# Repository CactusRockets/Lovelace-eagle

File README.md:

# Placas da aviônica para o foguete Lovelace-1KM

Nesse repositório temos os arquivos das placas que farão parte da aviônica do foguete Lovelace de 1km da Cactus Rockets Design.

### Descrição

Temos duas placas principais para esta aviônica:
- Placa de Processamento
- Placa de Acionamento

A placa de processamento é responsável pelo processamento dos dados dos módulos, armazenamento desses dados e telemetria. A placa de acionamento possui o circuito necessário para a correta ativação do Skib.

OBS.: Os arquivos das placas podems ser abertos por meio software Eagle da Autodesk.

### Esquemáticos e layouts

### Conexões entre placas

### Funcionamento

A placa de processamento contém um switch de ativação do sistema. No momento que o switch é pressionado, o sistema liga e faz a leitura dos módulos. Após cada leitura, ele armazena esses valores no microSD e envia esses dados via telemetria.

No momento que a placa de processamento detectar uma queda, ela envia um sinal para a placa de acionamento para que a mesma ative o Skib da parte de recuperação.

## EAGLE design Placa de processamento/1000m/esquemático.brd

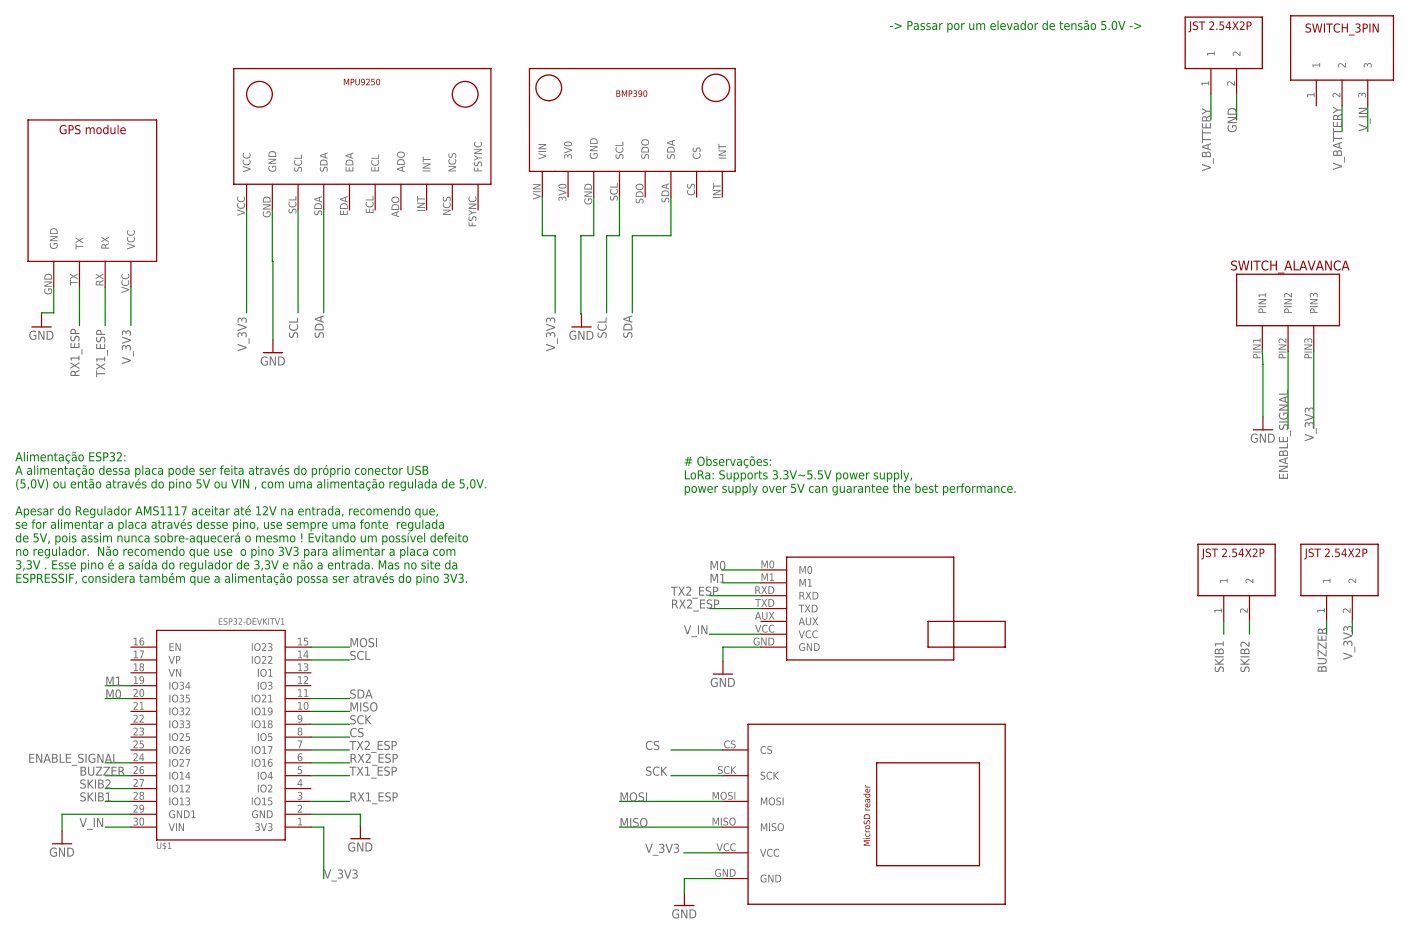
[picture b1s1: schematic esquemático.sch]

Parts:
U$1: ESP32DEVKITV1; ESP32-DEVKITV1
U$2: E22-400T30D; E22-400T30D_FOOTPRINT
U$3: GPS_MODULE; GPS_MODULE_FOOTPRINT
U$5: SWITCH_ALAVANCA; SWITCH_ALAVANCA_FOOTPRINT
U$7: MICROSD_READER; MICROSD_READER_FOOTPRINT
U$8, U$9, U$12: JST2.54X2P; JST2.54X2P_FOOTPRINT
U$10: MPU9250V1; MPU9250_FOOTPRINT
U$11: SWITCH_3PIN
U$13: BMP390V1; BMP390_FOOTPRINT

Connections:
BUZZER: U$1.26 (IO14), U$9.1
CS: U$1.8 (IO5), U$7.CS
ENABLE_SIGNAL: U$1.24 (IO27), U$5.PIN2
GND: U$1.2 (GND), U$1.29 (GND1), U$2.GND, U$3.GND, U$5.PIN1, U$7.GND, U$10.GND, U$12.2, U$13.GND
M0: U$1.20 (IO35), U$2.M0
M1: U$1.19 (IO34), U$2.M1
MISO: U$1.10 (IO19), U$7.MISO
MOSI: U$1.15 (IO23), U$7.MOSI
RX1_ESP: U$1.3 (IO15), U$3.TX
RX2_ESP: U$1.6 (IO16), U$2.TXD
SCK: U$1.9 (IO18), U$7.SCK
SCL: U$1.14 (IO22), U$10.SCL, U$13.SCL
SDA: U$1.11 (IO21), U$10.SDA, U$13.SDA
SKIB1: U$1.28 (IO13), U$8.1
SKIB2: U$1.27 (IO12), U$8.2
TX1_ESP: U$1.5 (IO4), U$3.RX
TX2_ESP: U$1.7 (IO17), U$2.RXD
V_3V3: U$1.1 (3V3), U$3.VCC, U$5.PIN3, U$7.VCC, U$9.2, U$10.VCC, U$13.VIN
V_BATTERY: U$11.2, U$12.1
V_IN: U$1.30 (VIN), U$2.VCC, U$11.3

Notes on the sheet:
-> Passar por um elevador de tensão 5.0V ->
# Observações: LoRa: Supports 3.3V~5.5V power supply, power supply over 5V can guarantee the best performance.
Alimentação ESP32: A alimentação dessa placa pode ser feita através do próprio conector USB (5,0V) ou então através do pino 5V ou VIN , com uma alimentação regulada de 5,0V. Apesar do Regulador AMS1117 aceitar até 12V na entrada, recomendo que, se for alimentar a placa através desse pino, use sempr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

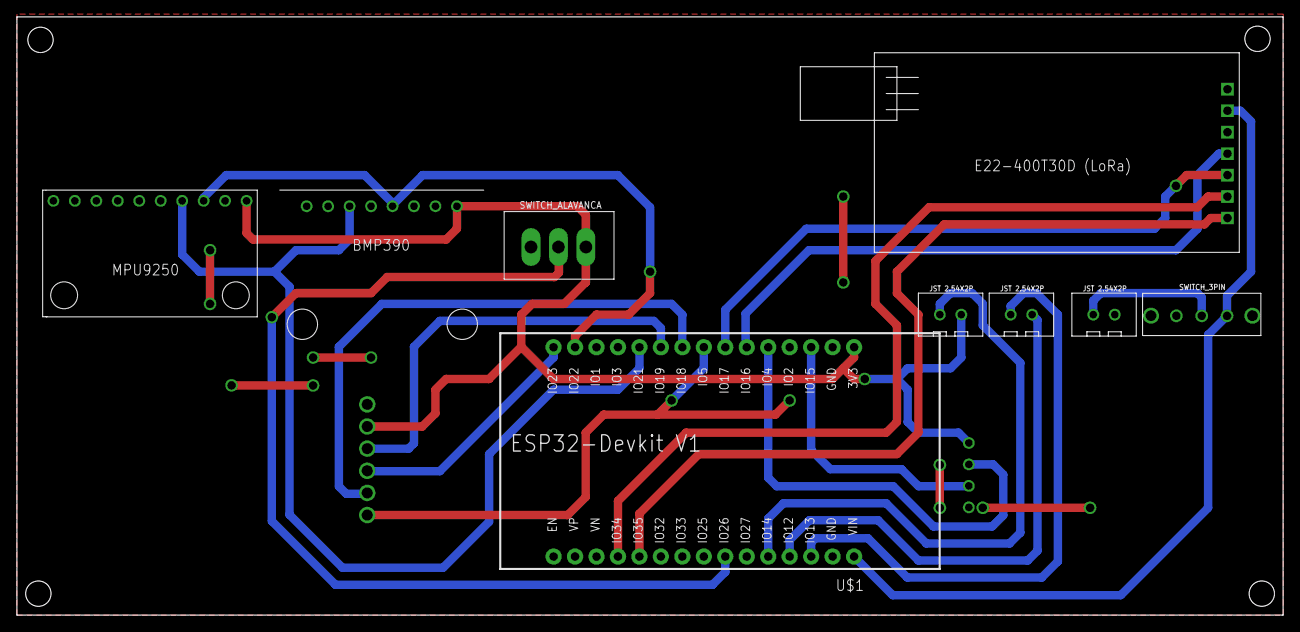
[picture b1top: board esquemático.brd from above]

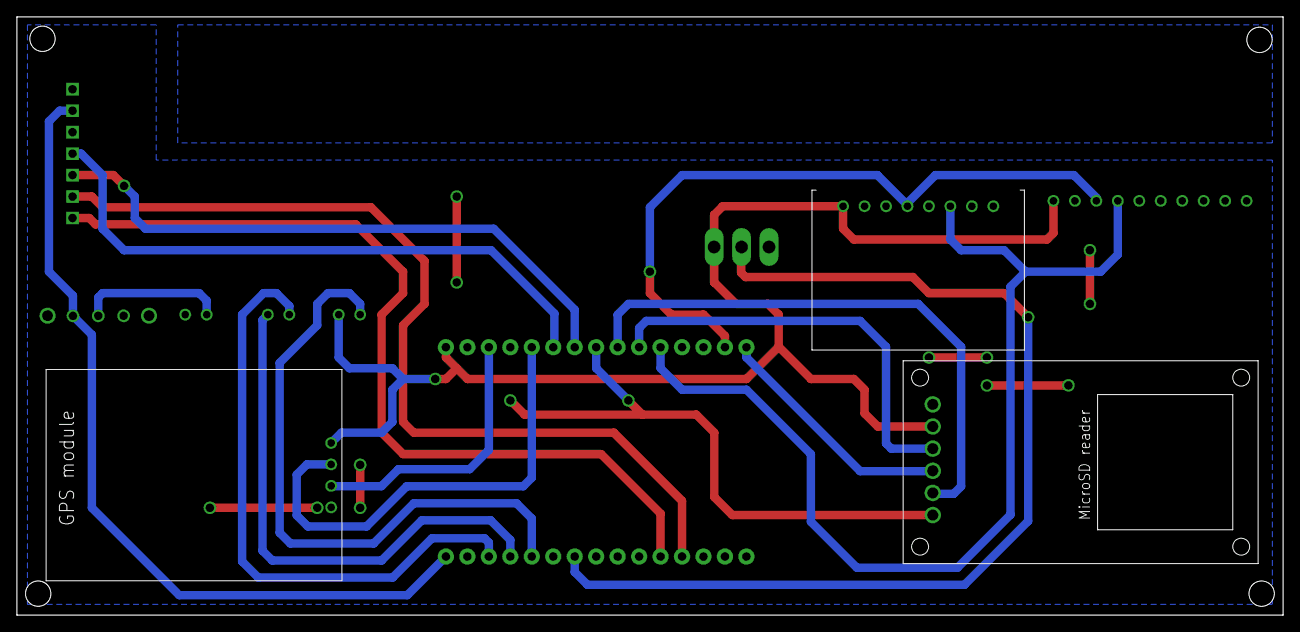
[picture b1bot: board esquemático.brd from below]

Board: 2 copper layers, 149.8 x 70.8 mm, 11 parts (2 on the bottom side), 20 nets.

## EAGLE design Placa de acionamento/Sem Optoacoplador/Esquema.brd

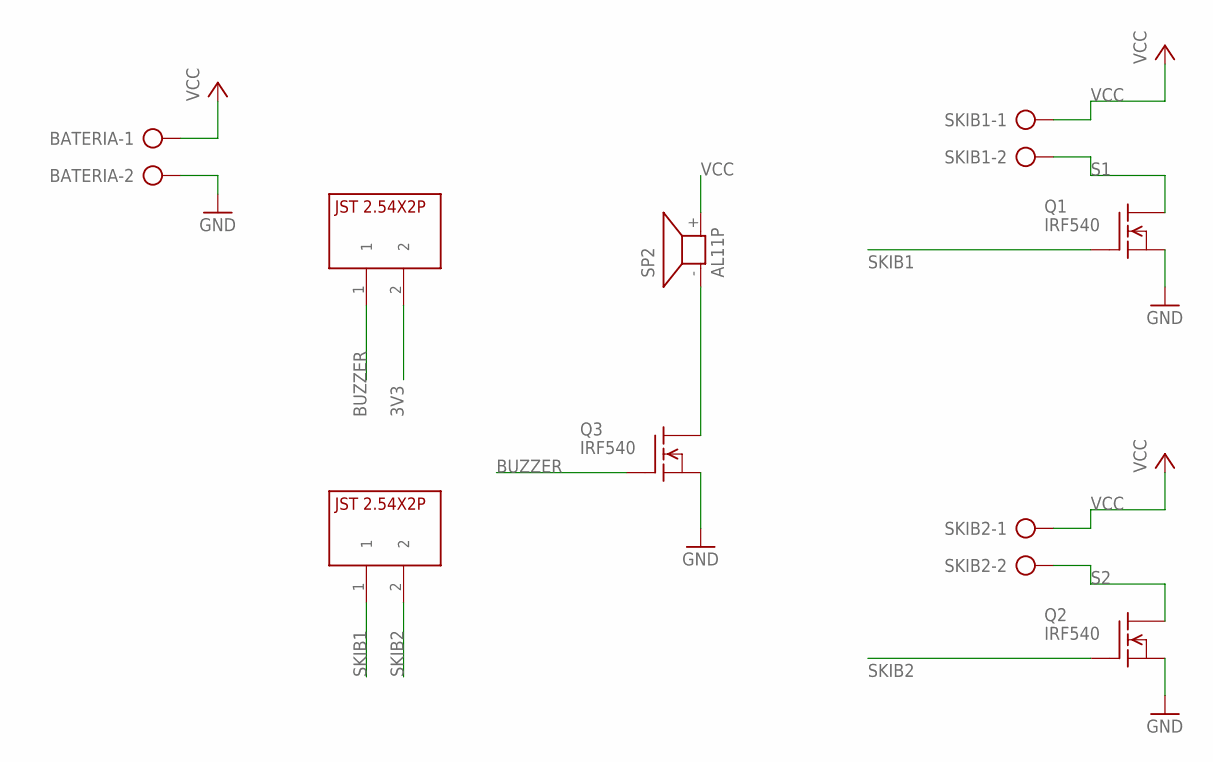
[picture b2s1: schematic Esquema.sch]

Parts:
BATERIA: AK500/2-H
Q1, Q2, Q3: IRF540; TO220
SKIB1, SKIB2: AK500/2-H
SP2: AL11P
U$1, U$2: JST2.54X2P; JST2.54X2P_FOOTPRINT

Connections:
3V3: U$1.2
BUZZER: Q3.1 (G), U$1.1
GND: BATERIA.2, Q1.3 (S), Q2.3 (S), Q3.3 (S)
unnamed: Q3.2 (D), SP2.- (1)
S1: Q1.2 (D), SKIB1.2
S2: Q2.2 (D), SKIB2.2
SKIB1: Q1.1 (G), U$2.1
SKIB2: Q2.1 (G), U$2.2
VCC: BATERIA.1, SKIB1.1, SKIB2.1, SP2.+ (2)

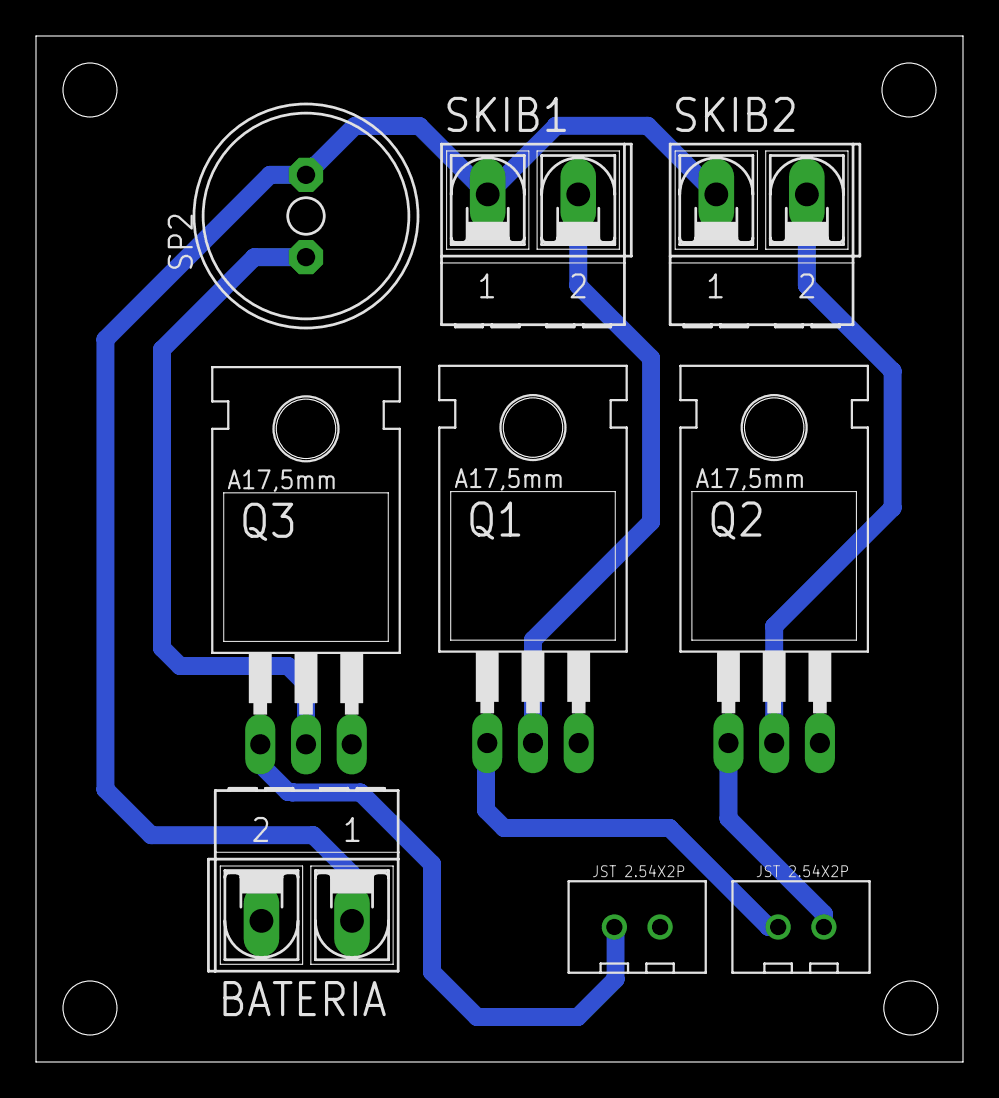
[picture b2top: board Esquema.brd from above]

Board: 2 copper layers, 51.5 x 57.0 mm, 9 parts (0 on the bottom side), 8 nets.
